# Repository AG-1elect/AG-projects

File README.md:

# AG Projects

**Public collection of Adam’s engineering project files**

A curated archive of CAD models, PCB designs, schematics, firmware, photographs, and build notes from electronics and engineering projects.

## Project areas

| Area | Description |
|---|---|
| [Electronics](Electronics/) | Circuits, PCB designs, power supplies, and electronic builds |
| [Mechatronics](Mechatronics/) | Projects combining mechanical design, electronics, and control |
| [3D Printing](3D-printing/) | Printable models, CAD parts, and practical accessories |
| [Others](Others/) | Experiments and projects outside the main categories |

## Repository contents

Projects may include:

- CAD and 3D models
- Schematics and PCB layouts
- Wiring diagrams
- Firmware and source code
- Enclosures and printed parts
- Photographs and assembly notes
- Calculations and test results
- Component lists and measurements

The files provided vary by project.

## Getting started

1. Browse a project category.
2. Open the relevant project folder.
3. Review its documentation and diagrams before use.
4. Check component ratings, power requirements, and any safety considerations.

## Safety notice

Some projects involve mains electricity, high currents, batteries, or rotating machinery.

These materials are provided for educational and reference purposes. Always verify the design independently, use appropriate protective equipment, and take reasonable safety precautions. Do not connect or operate unfamiliar circuits until you understand them.

## Contributing

Suggestions, corrections, and improvements are welcome. Please open an issue or submit a pull request with a clear description of the proposed change.

## License

A custom noncommercial license applies to the files in this repository.

You may download, study, modify, and use the files for personal, educational, and noncommercial purposes.
Commercial use is prohibited. This includes selling project designs or products made from this repository, or using the work to generate commercial revenue.
Videos, presentations, and other public content featuring a project must mention Adam and link to this repository: github.com/AG-1elect/AG-projects
Derivative projects must retain this repository's attribution.
Redistribution must include a copy of this license.
The files are provided “as is,” without warranty. The author is not responsible for injury, damage, or loss resulting from use.
Commercial use or licensing inquiries should be directed to the repository owner.

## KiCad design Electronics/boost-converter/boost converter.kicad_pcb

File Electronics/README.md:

# Electronics

This is where I document my work in electronics, from early circuit sketches and calculations to PCB layouts and bench measurements. I’m interested in how a circuit works, why a design choice makes sense, and what changes when the circuit meets real hardware.

## Using this repository

Browse the folders by topic. Each folder keeps related files together. When a folder includes a README, start there for design notes, file descriptions, and guidance on opening the files.

For KiCad designs, keep the project files in the same directory and open the `.kicad_pro` file to access the schematic and PCB layout.

## Reading the results

Calculated values describe what I expect from the design. Simulations show how a model behaves under specific conditions. Bench measurements show what happened on physical hardware. I distinguish these in the notes so you can tell what has been verified and what still needs testing.

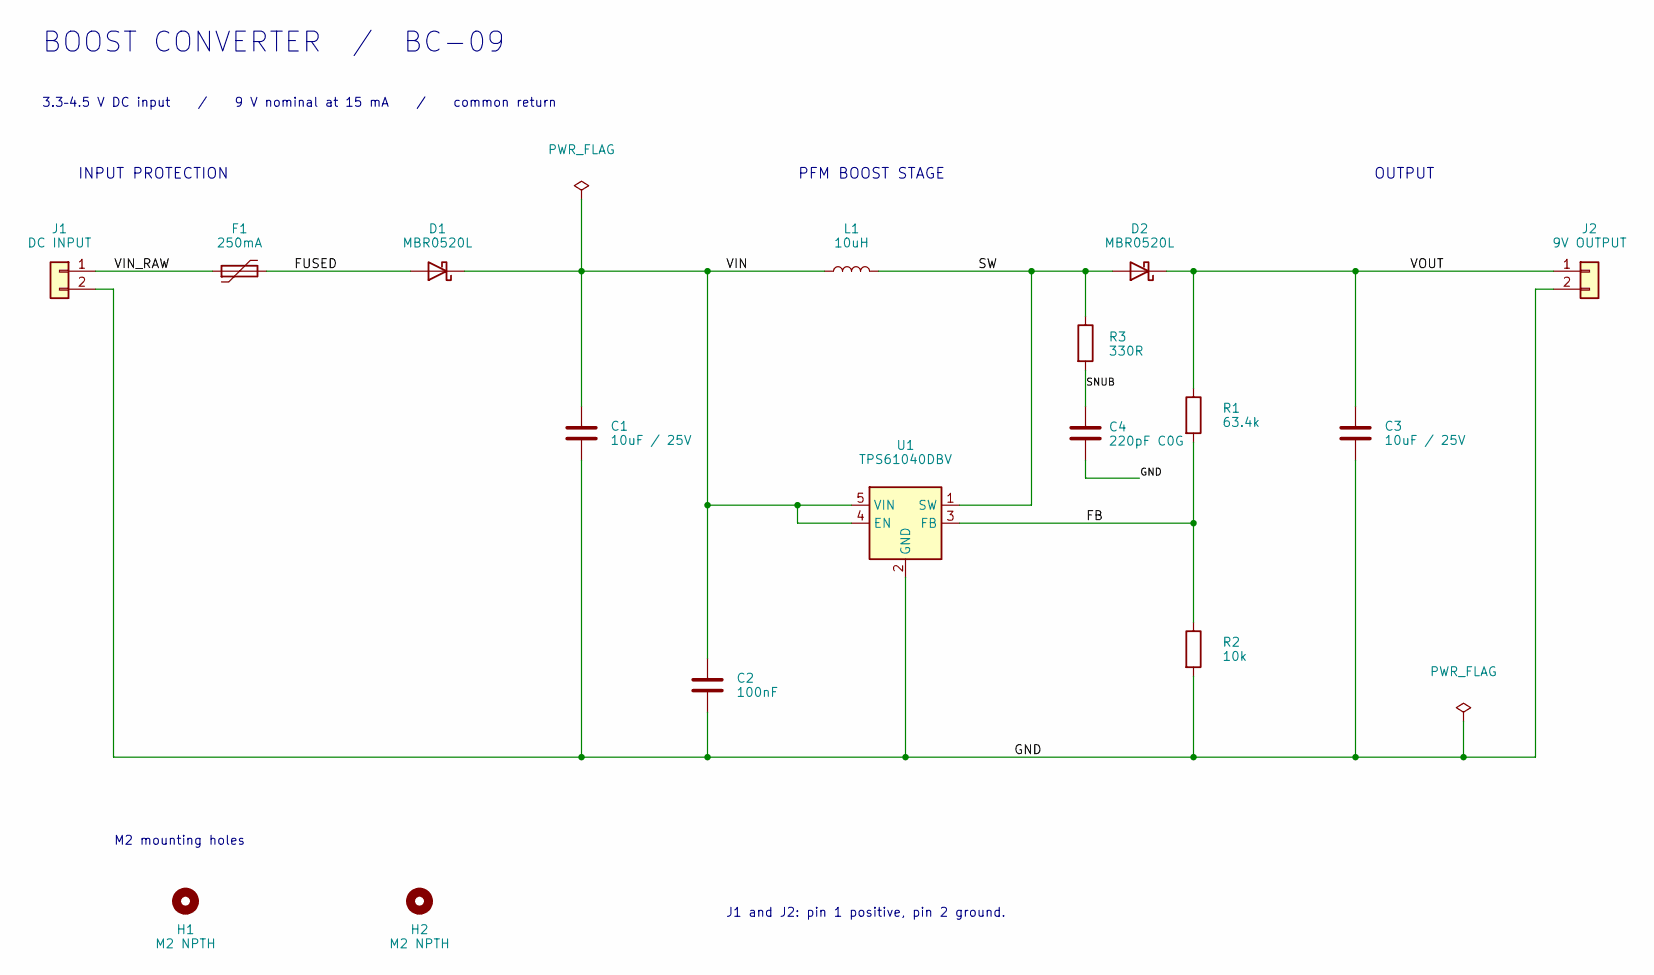
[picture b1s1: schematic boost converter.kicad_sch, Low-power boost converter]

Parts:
C1, C3: 10uF / 25V; C_1210_3225Metric; MPN GRM32ER71E106KA12L
C2: 100nF; C_0603_1608Metric; MPN GRM188R71C104KA01D
C4: 220pF C0G; C_0603_1608Metric; MPN GRM1885C1H221JA01D
D1, D2: MBR0520L; D_SOD-123; MPN MBR0520LT1G
F1: 250mA; Fuse_1206_3216Metric; MPN 1206L025YR
H1, H2: M2 NPTH; MountingHole_2.2mm_M2
J1: DC INPUT; PinHeader_1x02_P2.54mm_Vertical; MPN TSW-102-07-G-S
J2: 9V OUTPUT; PinHeader_1x02_P2.54mm_Vertical; MPN TSW-102-07-G-S
L1: 10uH; L_Coilcraft_XAL4040-XXX; MPN XAL4040-103MEC
R1: 63.4k; R_0603_1608Metric; MPN RC0603FR-0763K4L
R2: 10k; R_0603_1608Metric; MPN RC0603FR-0710KL
R3: 330R; R_0603_1608Metric; MPN RC0603FR-07330RL
U1: TPS61040DBV; SOT-23-5; MPN TPS61040DBVR

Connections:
/FB: R1.2, R2.1, U1.3 (FB)
/FUSED: D1.2 (A), F1.2
/GND: C1.2, C2.2, C3.2, C4.2, J1.2, J2.2, R2.2, U1.2 (GND)
/SNUB: C4.1, R3.2
/SW: D2.2 (A), L1.2, R3.1, U1.1 (SW)
/VIN: C1.1, C2.1, D1.1 (K), L1.1, U1.4 (EN), U1.5 (VIN)
/VIN_RAW: F1.1, J1.1
/VOUT: C3.1, D2.1 (K), J2.1, R1.1

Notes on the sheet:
BOOST CONVERTER / BC-09
3.3–4.5 V DC input / 9 V nominal at 15 mA / common return
INPUT PROTECTION
PFM BOOST STAGE
OUTPUT
M2 mounting holes
J1 and J2: pin 1 positive, pin 2 ground.

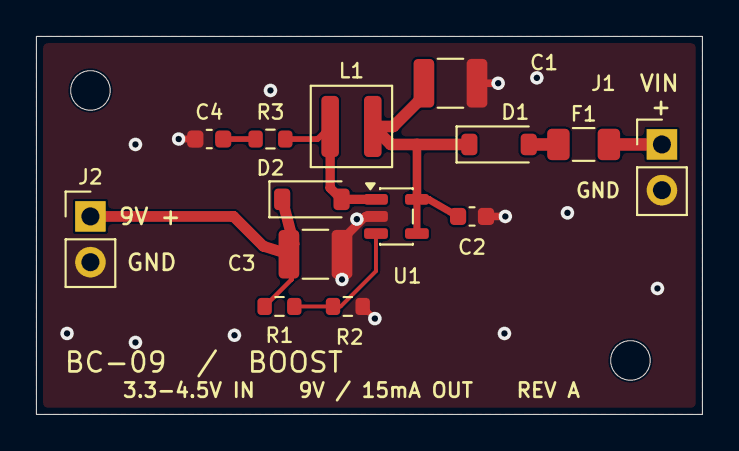
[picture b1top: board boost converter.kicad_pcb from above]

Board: 2 copper layers, 37.0 x 21.0 mm, 16 parts (0 on the bottom side), 8 nets.
